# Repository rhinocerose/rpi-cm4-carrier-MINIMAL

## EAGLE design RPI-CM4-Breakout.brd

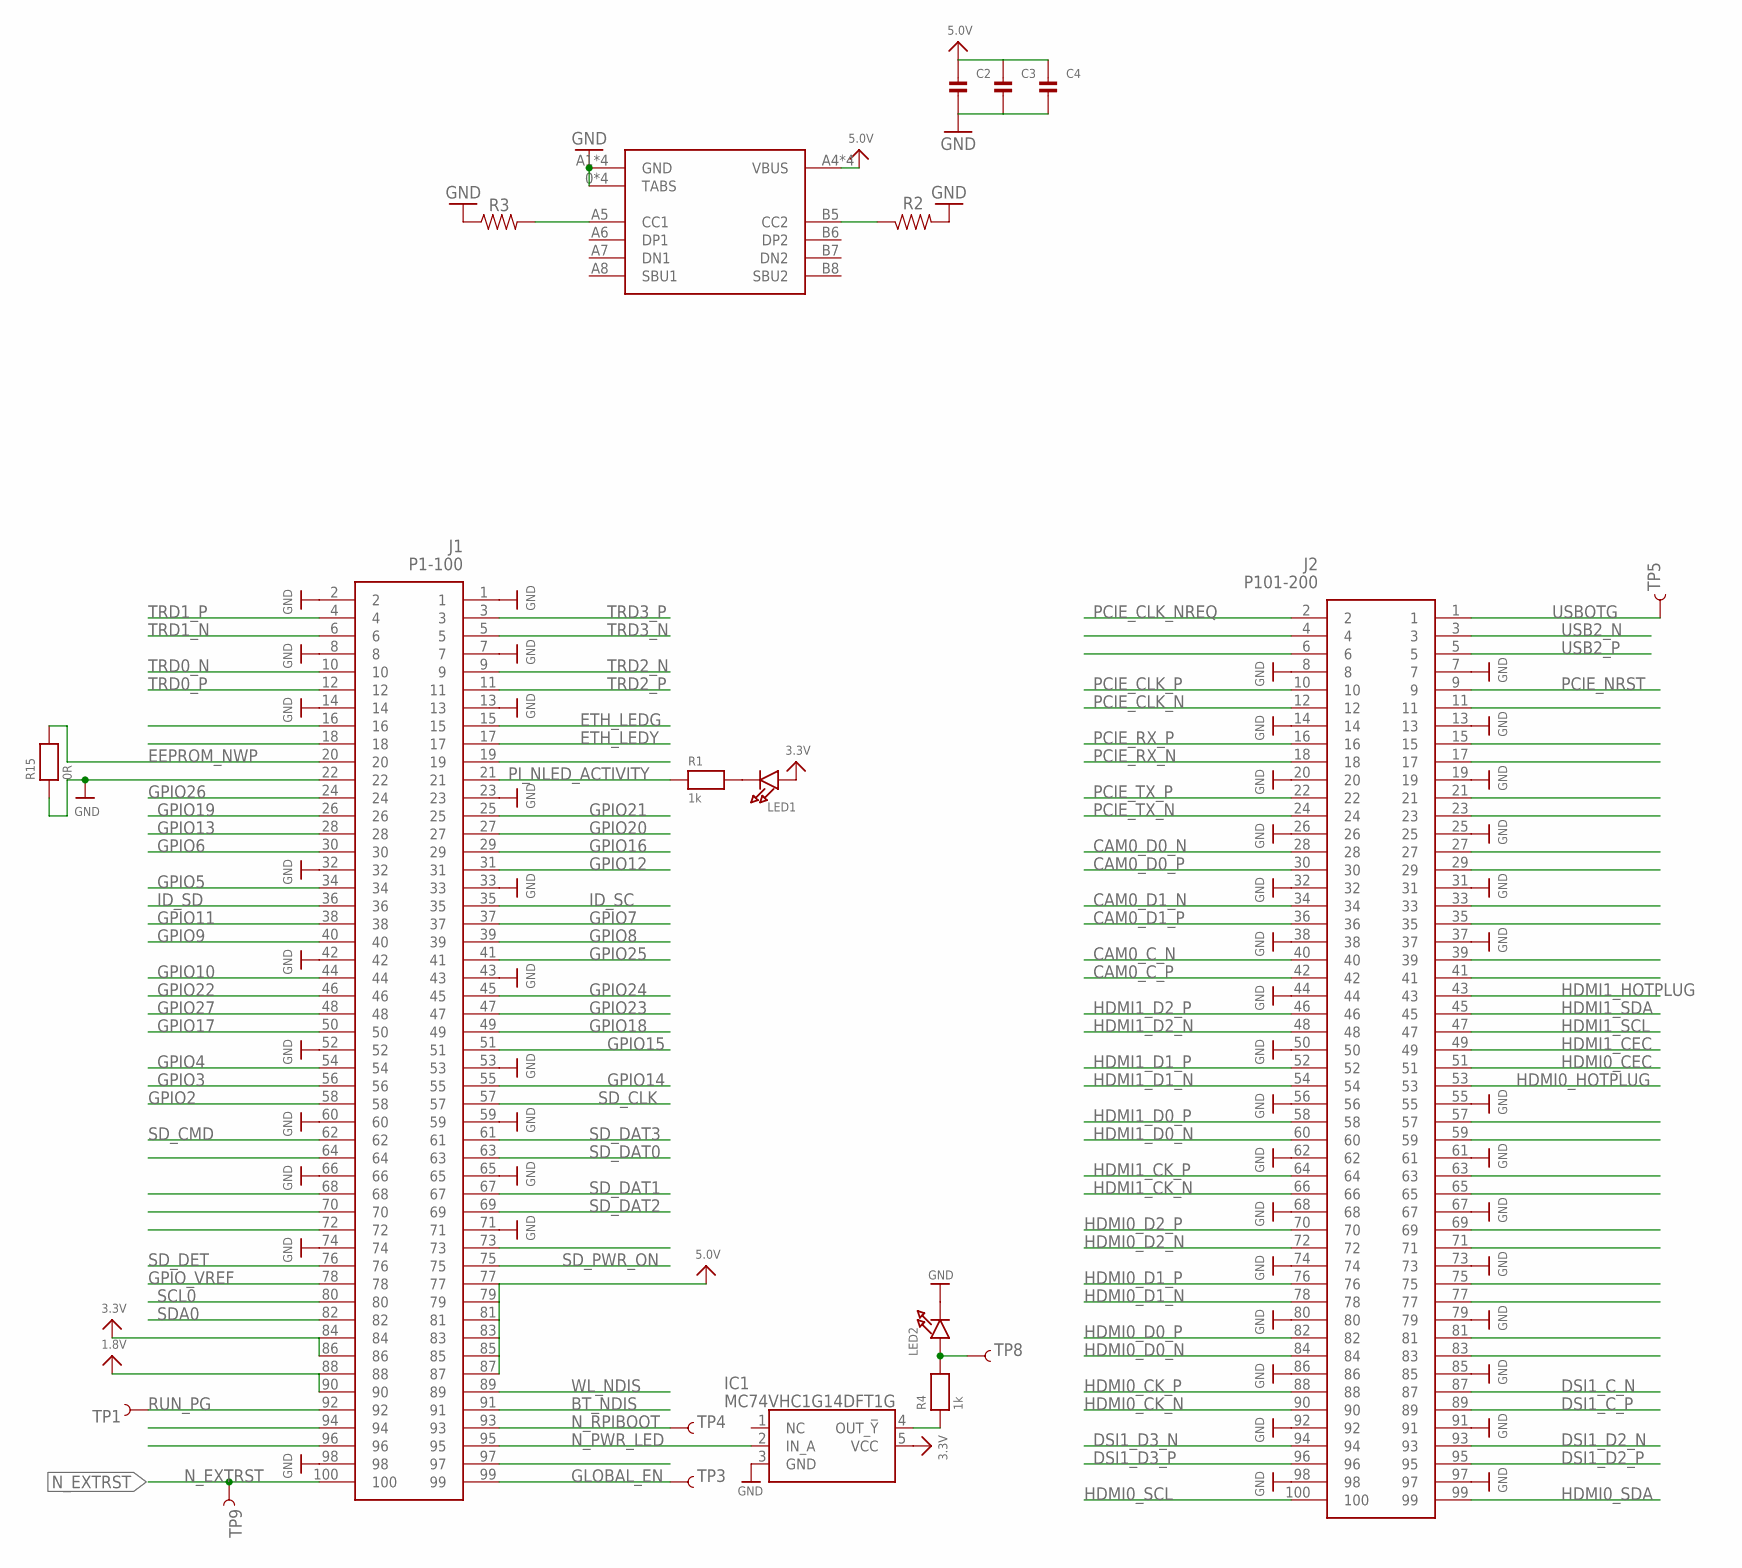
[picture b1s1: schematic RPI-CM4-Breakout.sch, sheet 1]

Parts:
C2, C3, C4: CAP_CERAMIC0402; 0402
IC1: MC74VHC1G14DFT1G; SOT65P210X110-5N
J1: P1-100; DF40C100DS04V51
J2: P101-200; DF40C100DS04V51
LED1, LED2: LED0603; CHIPLED_0603
R1, R4: 1k; _0402MP
R2, R3: 0603
R15: 0R; _0402MP
TP1, TP3, TP4, TP5, TP8, TP9: TEST-POINT3X5; PAD.03X.05
U$59: TYPE-C-31-M-12; USB-TYPE-C_16PIN-MALE-TYPE-C-31-M-12

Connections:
1.8V: J1.88, J1.90
3.3V: IC1.5 (VCC), J1.84, J1.86, LED1.A; also elsewhere on the board
5.0V: C2.1, C3.1, C4.1, J1.77, J1.79, J1.81, J1.83, J1.85, J1.87, U$59.A4 (VBUS), U$59.A9 (VBUS), U$59.B4 (VBUS), U$59.B9 (VBUS); also elsewhere on the board
A0/CC2: R3.2, U$59.A5 (CC1)
A3/CC1: R2.1, U$59.B5 (CC2)
BT_NDIS: J1.91
CAM0_C_N: J2.40
CAM0_C_P: J2.42
CAM0_D0_N: J2.28
CAM0_D0_P: J2.30
CAM0_D1_N: J2.34
CAM0_D1_P: J2.36
DSI1_C_N: J2.87
DSI1_C_P: J2.89
DSI1_D2_N: J2.93
DSI1_D2_P: J2.95
DSI1_D3_N: J2.94
DSI1_D3_P: J2.96
EEPROM_NWP: J1.20, R15.2
ETH_LEDG: J1.15; also elsewhere on the board
ETH_LEDY: J1.17; also elsewhere on the board
GLOBAL_EN: J1.99, TP3.P$1
GND: C2.2, C3.2, C4.2, IC1.3 (GND), J1.1, J1.2, J1.7, J1.8, J1.13, J1.14, J1.22, J1.23, J1.32, J1.33, J1.42, J1.43, J1.52, J1.53, J1.59, J1.60, J1.65, J1.66, J1.71, J1.74, J1.98, J2.7, J2.8, J2.13, J2.14, J2.19, J2.20, J2.25, J2.26, J2.31, J2.32, J2.37, J2.38, J2.44, J2.50, J2.55, J2.56, J2.61, J2.62, J2.67, J2.68, J2.73, J2.74, J2.79, J2.80, J2.85, J2.86, J2.91, J2.92, J2.97, J2.98, LED2.C, R2.2, R3.1, R15.1, U$59.0 (TABS), U$59.0-1 (TABS), U$59.0-2 (TABS), U$59.0-3 (TABS), U$59.A1 (GND), U$59.A12 (GND), U$59.B1 (GND), U$59.B12 (GND); also elsewhere on the board
GPIO2: J1.58
GPIO3: J1.56
GPIO4: J1.54
GPIO5: J1.34
GPIO6: J1.30
GPIO7: J1.37
GPIO8: J1.39
GPIO9: J1.40
GPIO10: J1.44
GPIO11: J1.38
GPIO12: J1.31
GPIO13: J1.28
GPIO14: J1.55
GPIO15: J1.51
GPIO16: J1.29
GPIO17: J1.50
GPIO18: J1.49
GPIO19: J1.26
GPIO20: J1.27
GPIO21: J1.25
GPIO22: J1.46
GPIO23: J1.47
GPIO24: J1.45
GPIO25: J1.41
GPIO26: J1.24
GPIO27: J1.48
GPIO_VREF: J1.78
HDMI0_CEC: J2.51
HDMI0_CK_N: J2.90; also elsewhere on the board
HDMI0_CK_P: J2.88; also elsewhere on the board
HDMI0_D0_N: J2.84; also elsewhere on the board
HDMI0_D0_P: J2.82; also elsewhere on the board
HDMI0_D1_N: J2.78; also elsewhere on the board
HDMI0_D1_P: J2.76; also elsewhere on the board
HDMI0_D2_N: J2.72; also elsewhere on the board
HDMI0_D2_P: J2.70; also elsewhere on the board
HDMI0_HOTPLUG: J2.53; also elsewhere on the board
HDMI0_SCL: J2.100; also elsewhere on the board
HDMI0_SDA: J2.99; also elsewhere on the board
HDMI1_CEC: J2.49
HDMI1_CK_N: J2.66
HDMI1_CK_P: J2.64
HDMI1_D0_N: J2.60
HDMI1_D0_P: J2.58
HDMI1_D1_N: J2.54
HDMI1_D1_P: J2.52
HDMI1_D2_N: J2.48
HDMI1_D2_P: J2.46
HDMI1_HOTPLUG: J2.43
HDMI1_SCL: J2.47
HDMI1_SDA: J2.45
ID_SC: J1.35
ID_SD: J1.36
unnamed: LED1.C, R1.2
unnamed: IC1.4 (OUT_!Y), R4.1
unnamed: LED2.A, R4.2, TP8.P$1
N_EXTRST: J1.100, TP9.P$1; also elsewhere on the board
N_PWR_LED: IC1.2 (IN_A), J1.95
N_RPIBOOT: J1.93, TP4.P$1
PCIE_CLK_N: J2.12
PCIE_CLK_NREQ: J2.2
PCIE_CLK_P: J2.10
PCIE_NRST: J2.9
PCIE_RX_N: J2.18
PCIE_RX_P: J2.16
PCIE_TX_N: J2.24
PCIE_TX_P: J2.22
PI_NLED_ACTIVITY: J1.21, R1.1
RUN_PG: J1.92, TP1.P$1
SCL0: J1.80
SDA0: J1.82
SD_CLK: J1.57; also elsewhere on the board
SD_CMD: J1.62; also elsewhere on the board
SD_DAT0: J1.63; also elsewhere on the board
SD_DAT1: J1.67; also elsewhere on the board
SD_DAT2: J1.69; also elsewhere on the board
SD_DAT3: J1.61; also elsewhere on the board
SD_DET: J1.76
SD_PWR_ON: J1.75
TRD0_N: J1.10; also elsewhere on the board
TRD0_P: J1.12; also elsewhere on the board
TRD1_N: J1.6; also elsewhere on the board
TRD1_P: J1.4; also elsewhere on the board
TRD2_N: J1.9; also elsewhere on the board
TRD2_P: J1.11; also elsewhere on the board
TRD3_N: J1.5; also elsewhere on the board
TRD3_P: J1.3; also elsewhere on the board
USB2_N: J2.3; also elsewhere on the board
USB2_P: J2.5; also elsewhere on the board
USBOTG: J2.1, TP5.P$1; also elsewhere on the board
WL_NDIS: J1.89

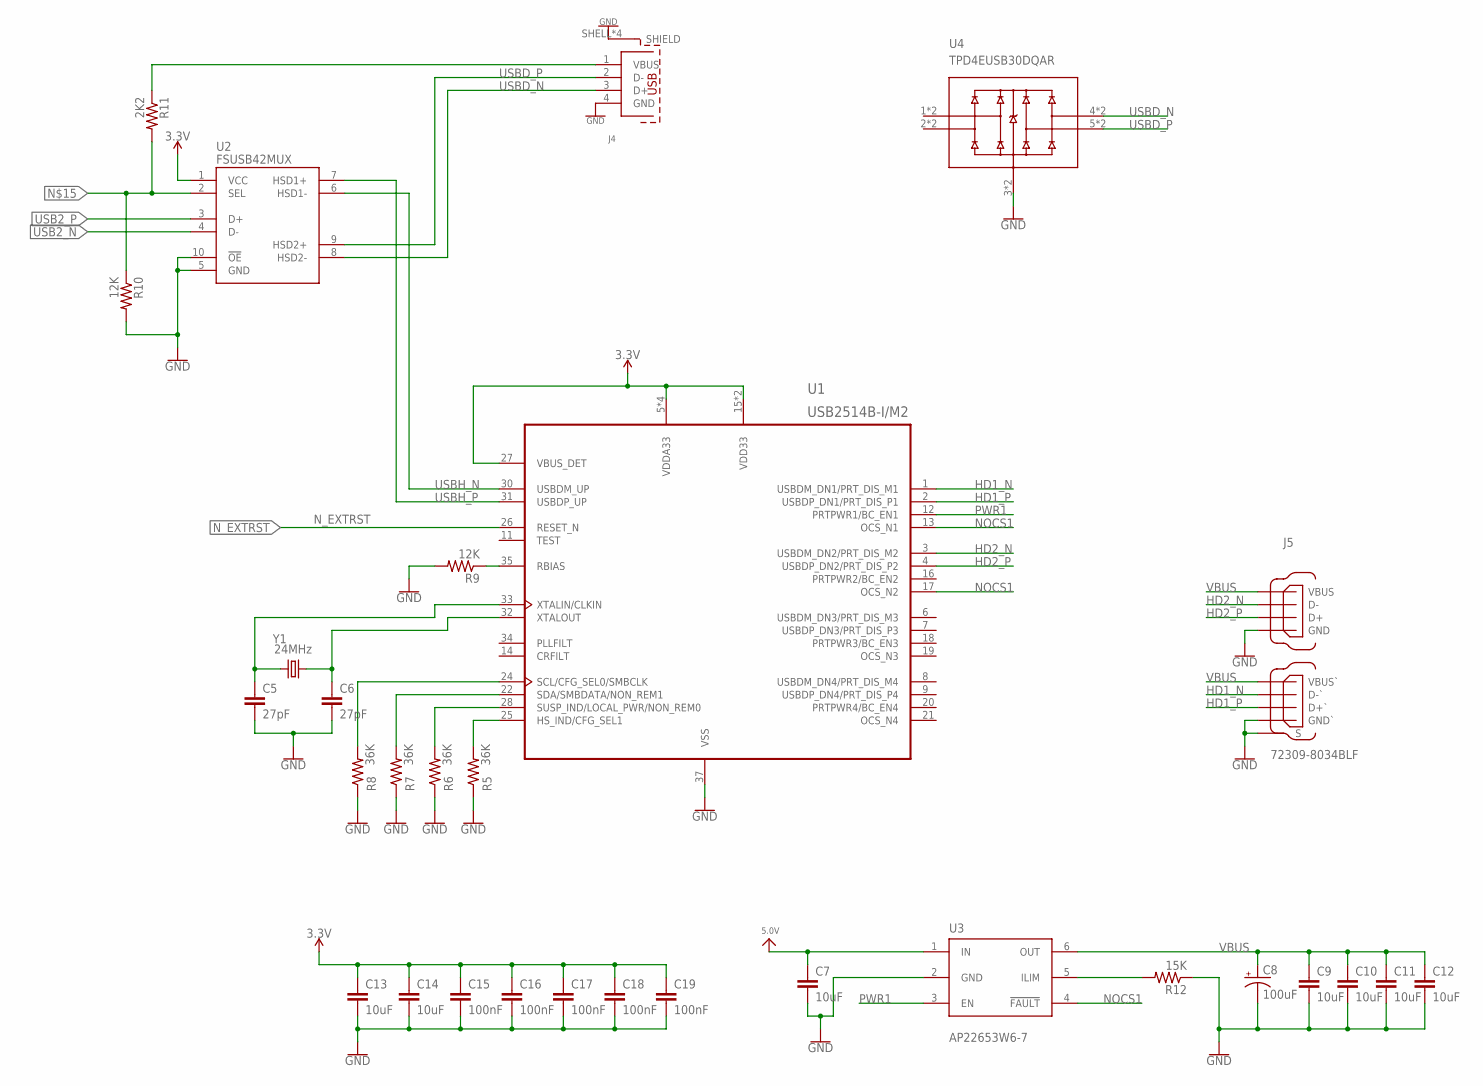
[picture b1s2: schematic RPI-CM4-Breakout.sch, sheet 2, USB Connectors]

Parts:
C5, C6: 27pF; C0603
C7, C9, C10, C11, C12, C13, C14: 10uF; C0805
C8: 100uF; EIA7343
C15, C16, C17, C18, C19: 100nF; C0603
J4: 629104190121
J5: 72309-8034BLF; FRAMATOME_72309-8034BLF
R5, R6, R7, R8: 36K; R0603
R9, R10: 12K; R0603
R11: 2K2; R0603
R12: 15K; R0603
U1: USB2514B-I/M2; QFN50P600X600X100-37N
U2: FSUSB42MUX; SOP50P490X110-10N
U3: AP22653W6-7; SOT95P280X145-6N
U4: TPD4EUSB30DQAR; IC_TPD4EUSB30DQAR
Y1: 24MHz; SM49

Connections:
3.3V: C13.1, C14.1, C15.1, C16.1, C17.1, C18.1, C19.1, U1.5 (VDDA33), U1.10 (VDDA33), U1.15 (VDD33), U1.23 (VDD33), U1.27 (VBUS_DET), U1.29 (VDDA33), U1.36 (VDDA33), U2.1 (VCC); also elsewhere on the board
5.0V: C7.1, U3.1 (IN); also elsewhere on the board
GND: C5.2, C6.2, C7.2, C8.C (-), C9.2, C10.2, C11.2, C12.2, C13.2, C14.2, C15.2, C16.2, C17.2, C18.2, C19.2, J4.4 (GND), J4.SHELL (SHIELD), J4.SHELL1 (SHIELD), J4.SHELL2 (SHIELD), J4.SHELL3 (SHIELD), J5.1 (S), J5.2 (S), J5.A4 (GND`), J5.B4 (GND), R5.1, R6.1, R7.1, R8.1, R9.2, R10.2, R12.1, U1.37 (VSS), U2.5 (GND), U2.10 (!OE), U3.2 (GND), U4.3 (GND_3), U4.8 (GND_3); also elsewhere on the board
HD1_N: J5.A2 (D-`), U1.1 (USBDM_DN1/PRT_DIS_M1)
HD1_P: J5.A3 (D+`), U1.2 (USBDP_DN1/PRT_DIS_P1)
HD2_N: J5.B2 (D-), U1.3 (USBDM_DN2/PRT_DIS_M2)
HD2_P: J5.B3 (D+), U1.4 (USBDP_DN2/PRT_DIS_P2)
unnamed: R5.2, U1.25 (HS_IND/CFG_SEL1)
unnamed: R6.2, U1.28 (SUSP_IND/LOCAL_PWR/NON_REM0)
unnamed: R7.2, U1.22 (SDA/SMBDATA/NON_REM1)
unnamed: R8.2, U1.24 (SCL/CFG_SEL0/SMBCLK)
unnamed: R9.1, U1.35 (RBIAS)
unnamed: C5.1, U1.33 (XTALIN/CLKIN), Y1.1
unnamed: C6.1, U1.32 (XTALOUT), Y1.2
unnamed: R10.1, R11.2, U2.2 (SEL)
unnamed: R12.2, U3.5 (ILIM)
NOCS1: U1.13 (OCS_N1), U1.17 (OCS_N2), U3.4 (!FAULT)
N_EXTRST: U1.26 (RESET_N); also elsewhere on the board
PWR1: U1.12 (PRTPWR1/BC_EN1), U3.3 (EN)
USB2_N: U2.4 (D-); also elsewhere on the board
USB2_P: U2.3 (D+); also elsewhere on the board
USBD_N: J4.3 (D+), U2.8 (HSD2-), U4.4 (D2+), U4.7 (D2+)
USBD_P: J4.2 (D-), U2.9 (HSD2+), U4.5 (D2-), U4.6 (D2-)
USBH_N: U1.30 (USBDM_UP), U2.6 (HSD1-)
USBH_P: U1.31 (USBDP_UP), U2.7 (HSD1+)
USBOTG: J4.1 (VBUS), R11.1; also elsewhere on the board
VBUS: C8.A (+), C9.1, C10.1, C11.1, C12.1, J5.A1 (VBUS`), J5.B1 (VBUS), U3.6 (OUT)

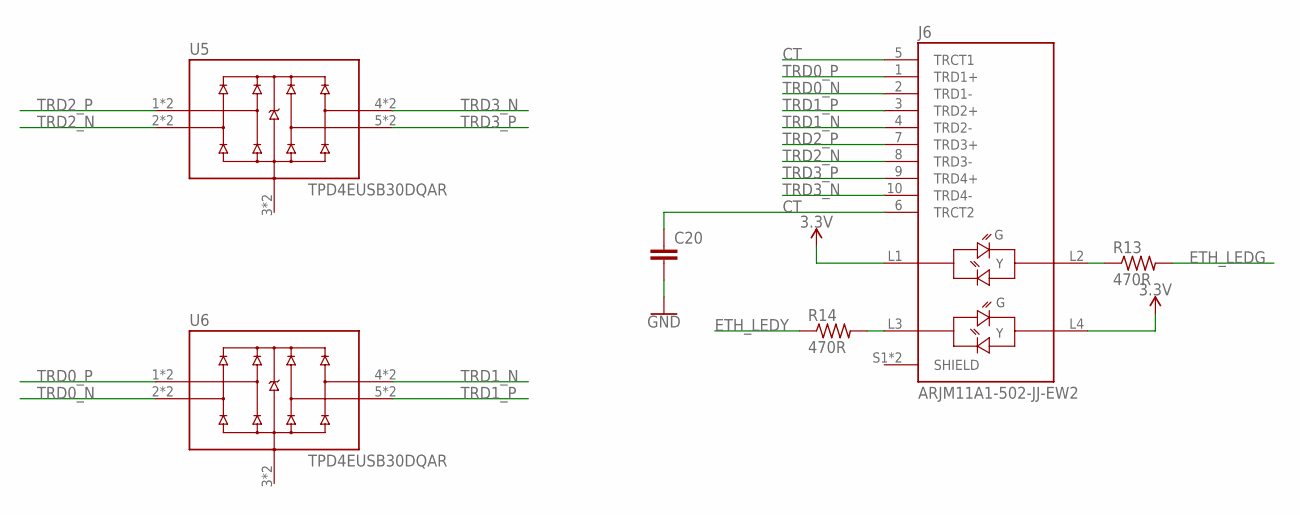
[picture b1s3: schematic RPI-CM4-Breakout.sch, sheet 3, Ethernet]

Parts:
C20: C-EUC0603; C0603
J6: ARJM11A1-502-JJ-EW2; ABRACON_ARJM11A1-502-JJ-EW2
R13, R14: 470R; R0603
U5, U6: TPD4EUSB30DQAR; IC_TPD4EUSB30DQAR

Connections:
3.3V: J6.L1, J6.L4; also elsewhere on the board
CT: C20.1, J6.5 (TRCT1), J6.6 (TRCT2)
ETH_LEDG: R13.2; also elsewhere on the board
ETH_LEDY: R14.1; also elsewhere on the board
GND: C20.2; also elsewhere on the board
GND_3: U5.3 (GND_3), U5.8 (GND_3), U6.3 (GND_3), U6.8 (GND_3)
unnamed: J6.L2, R13.1
unnamed: J6.L3, R14.2
TRD0_N: J6.2 (TRD1-), U6.2 (D1-), U6.9 (D1-); also elsewhere on the board
TRD0_P: J6.1 (TRD1+), U6.1 (D1+), U6.10 (D1+); also elsewhere on the board
TRD1_N: J6.4 (TRD2-), U6.4 (D2+), U6.7 (D2+); also elsewhere on the board
TRD1_P: J6.3 (TRD2+), U6.5 (D2-), U6.6 (D2-); also elsewhere on the board
TRD2_N: J6.8 (TRD3-), U5.2 (D1-), U5.9 (D1-); also elsewhere on the board
TRD2_P: J6.7 (TRD3+), U5.1 (D1+), U5.10 (D1+); also elsewhere on the board
TRD3_N: J6.10 (TRD4-), U5.4 (D2+), U5.7 (D2+); also elsewhere on the board
TRD3_P: J6.9 (TRD4+), U5.5 (D2-), U5.6 (D2-); also elsewhere on the board

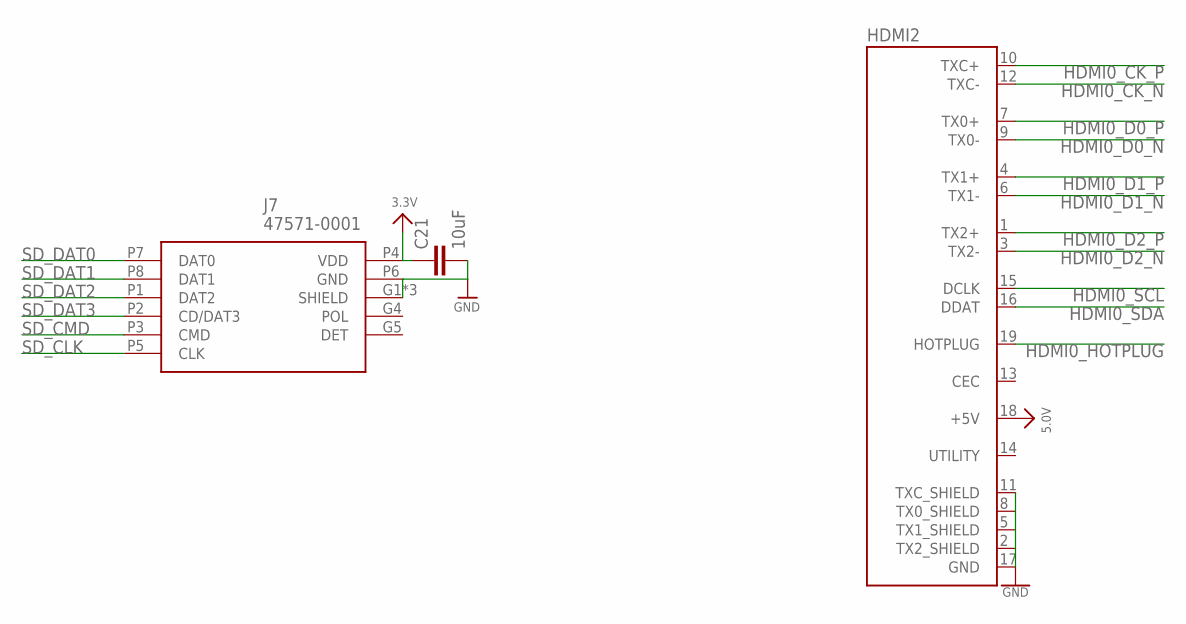
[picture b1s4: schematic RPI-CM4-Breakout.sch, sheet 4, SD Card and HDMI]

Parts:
C21: 10uF; 0603
HDMI2: HDMI_MOLEX_47151-0001
J7: 47571-0001

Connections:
3.3V: C21.1, J7.P4 (VDD); also elsewhere on the board
5.0V: HDMI2.18 (+5V); also elsewhere on the board
GND: C21.2, HDMI2.2 (TX2_SHIELD), HDMI2.5 (TX1_SHIELD), HDMI2.8 (TX0_SHIELD), HDMI2.11 (TXC_SHIELD), HDMI2.17 (GND), HDMI2.P$1 (GND), HDMI2.P$2 (GND), HDMI2.P$3 (GND), HDMI2.P$4 (GND), J7.G1 (SHIELD), J7.G2 (SHIELD), J7.G3 (SHIELD), J7.P6 (GND); also elsewhere on the board
HDMI0_CK_N: HDMI2.12 (TXC-); also elsewhere on the board
HDMI0_CK_P: HDMI2.10 (TXC+); also elsewhere on the board
HDMI0_D0_N: HDMI2.9 (TX0-); also elsewhere on the board
HDMI0_D0_P: HDMI2.7 (TX0+); also elsewhere on the board
HDMI0_D1_N: HDMI2.6 (TX1-); also elsewhere on the board
HDMI0_D1_P: HDMI2.4 (TX1+); also elsewhere on the board
HDMI0_D2_N: HDMI2.3 (TX2-); also elsewhere on the board
HDMI0_D2_P: HDMI2.1 (TX2+); also elsewhere on the board
HDMI0_HOTPLUG: HDMI2.19 (HOTPLUG); also elsewhere on the board
HDMI0_SCL: HDMI2.15 (DCLK); also elsewhere on the board
HDMI0_SDA: HDMI2.16 (DDAT); also elsewhere on the board
SD_CLK: J7.P5 (CLK); also elsewhere on the board
SD_CMD: J7.P3 (CMD); also elsewhere on the board
SD_DAT0: J7.P7 (DAT0); also elsewhere on the board
SD_DAT1: J7.P8 (DAT1); also elsewhere on the board
SD_DAT2: J7.P1 (DAT2); also elsewhere on the board
SD_DAT3: J7.P2 (CD/DAT3); also elsewhere on the board

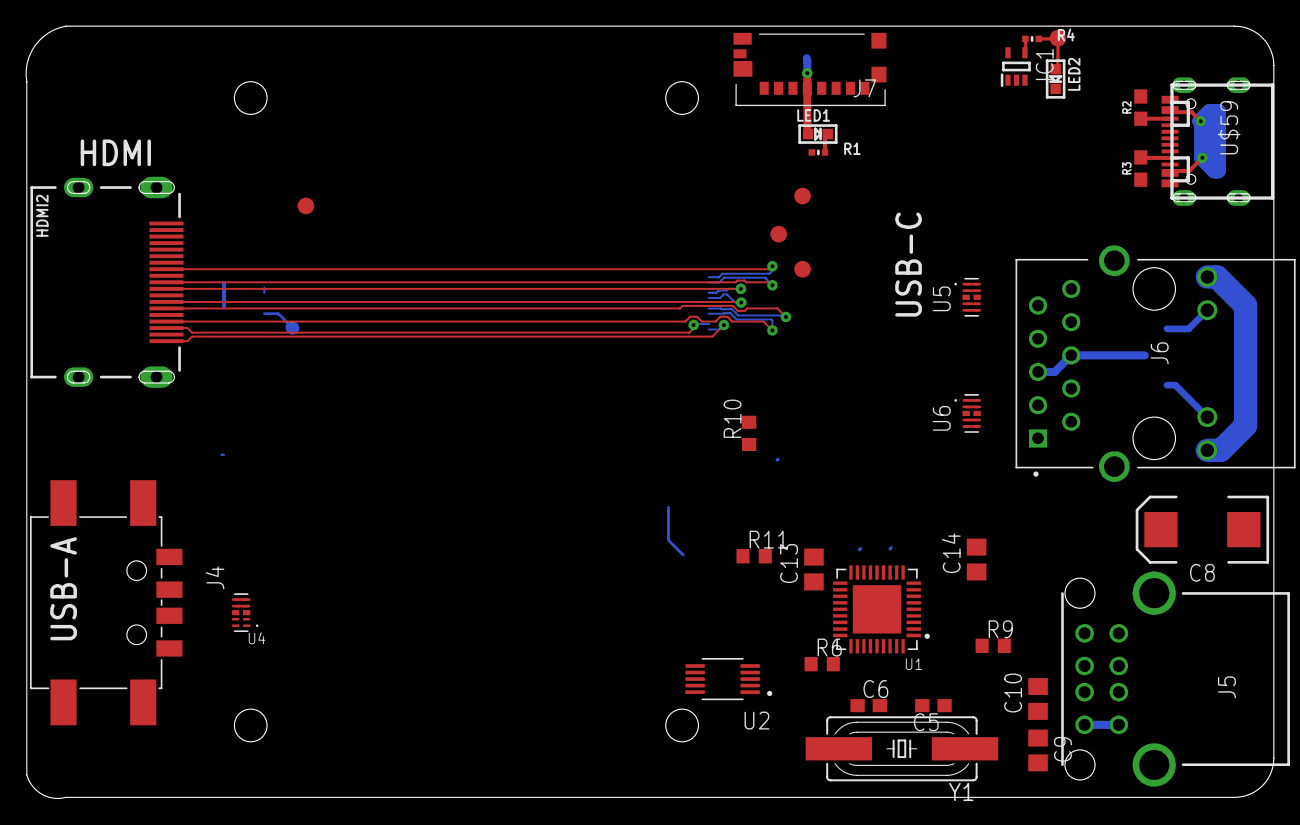
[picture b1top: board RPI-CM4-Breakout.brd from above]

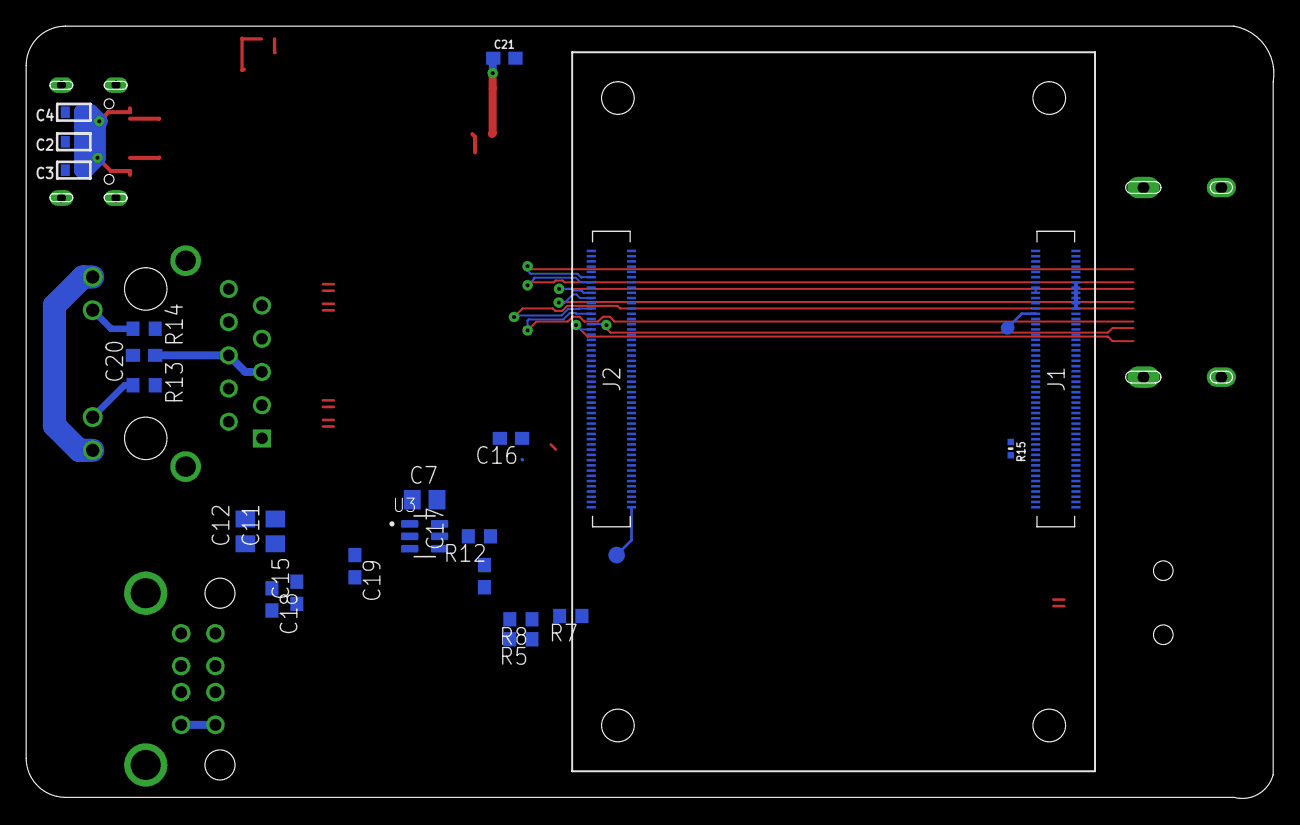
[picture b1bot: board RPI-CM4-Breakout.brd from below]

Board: 2 copper layers, 95.4 x 59.1 mm, 59 parts (24 on the bottom side), 70 nets.

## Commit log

2021-08-17 Added USB block
2021-08-17 Initial layout
2021-08-19 Moved CM4 to bottom side

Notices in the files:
parts and their libraries:
SparkFun-Capacitors: Licensing: Creative Commons ShareAlike 4.0 International - https://creativecommons.org/licenses/by-sa/4.0
microbuilder: This work is placed in the public domain, and may be freely used for commercial and non-commercial work with the following conditions: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
